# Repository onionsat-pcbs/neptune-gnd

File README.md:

# Neptune GND
Ground Station Module for Project Neptune

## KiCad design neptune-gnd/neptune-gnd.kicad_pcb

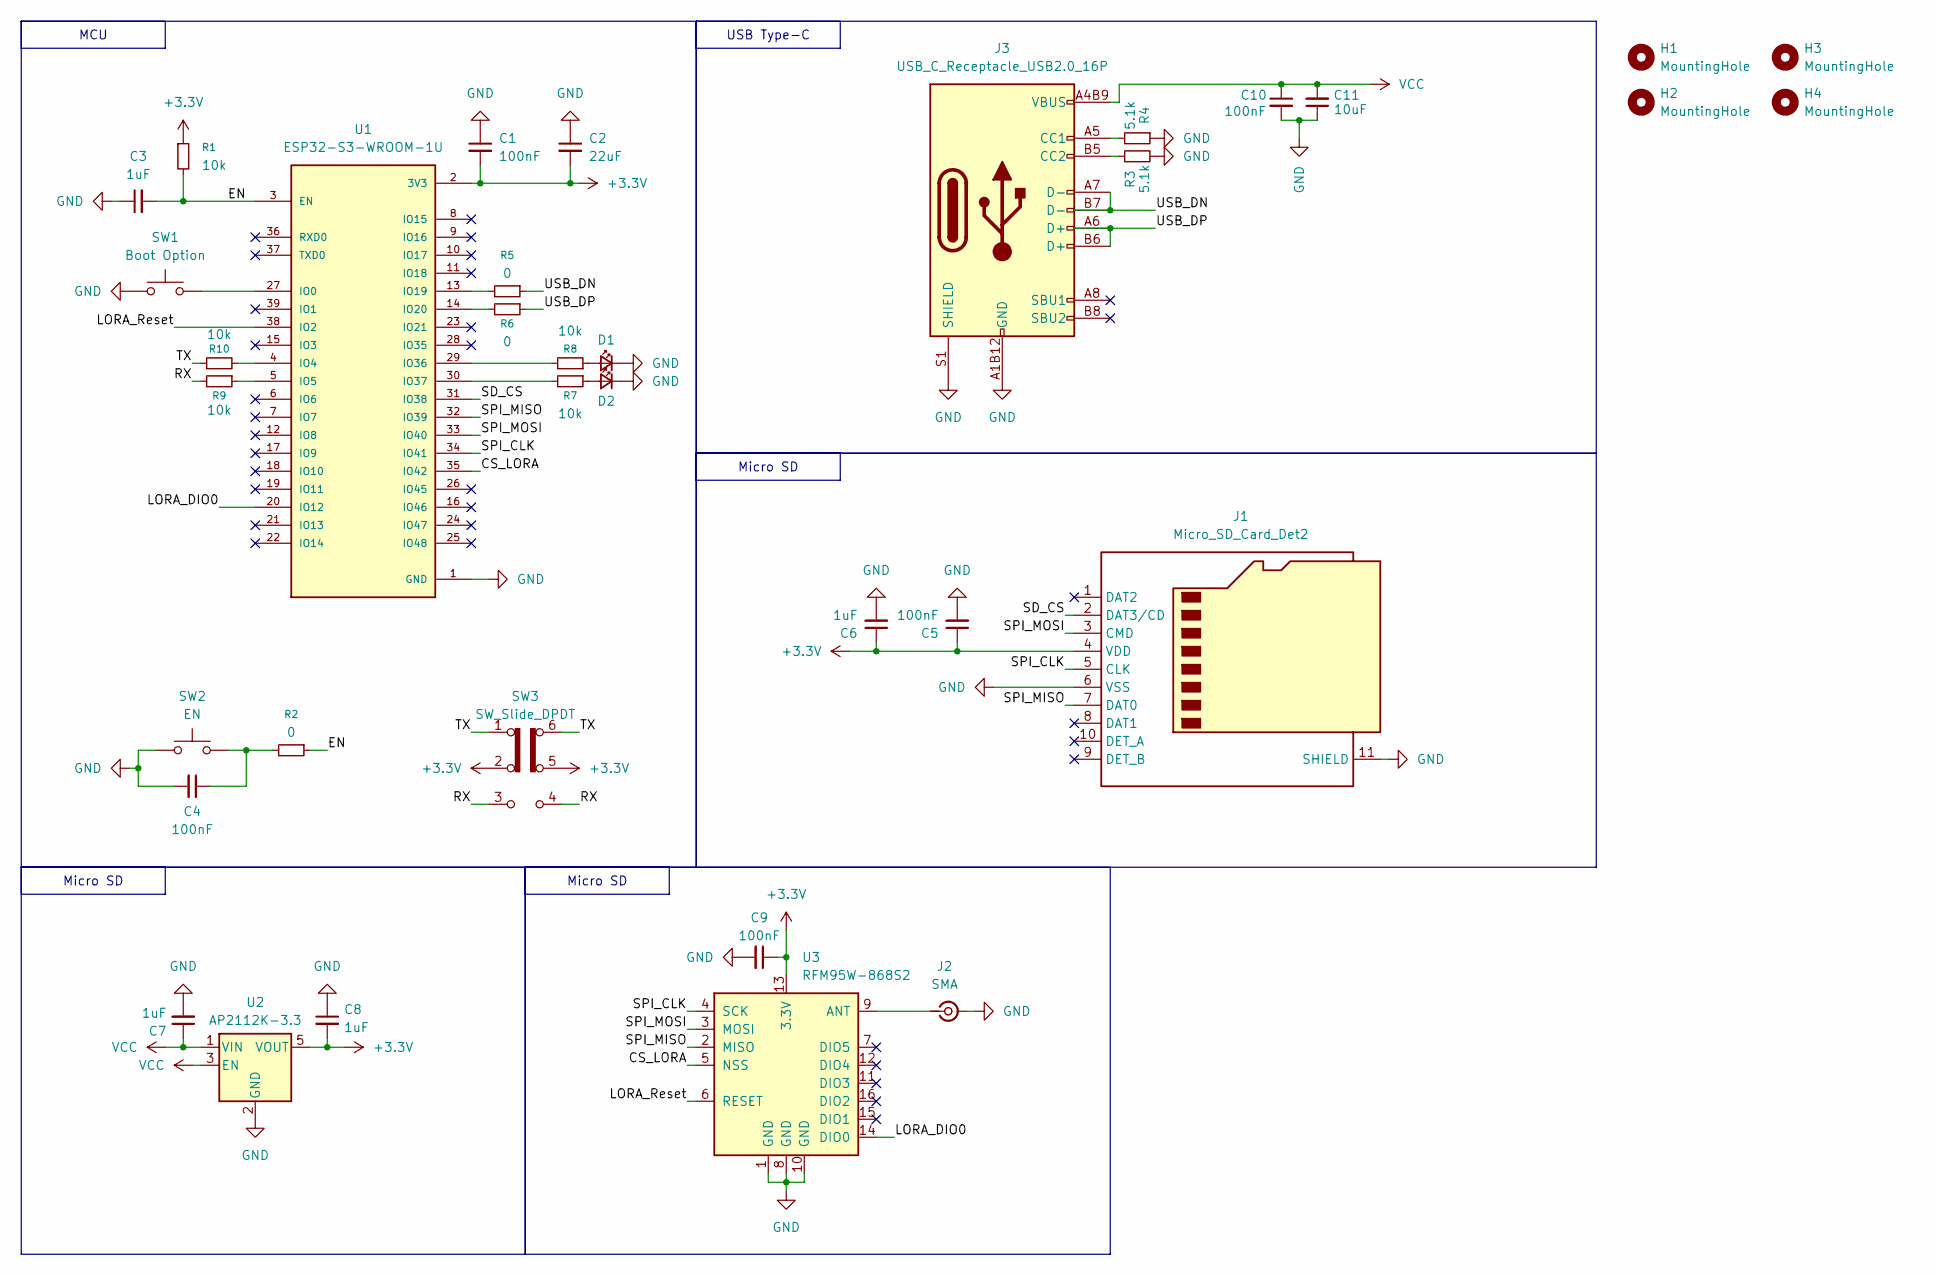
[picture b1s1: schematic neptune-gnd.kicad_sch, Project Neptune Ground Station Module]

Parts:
C1, C4, C5, C9, C10: 100nF; C_0603_1608Metric
C2: 22uF; C_0805_2012Metric
C3, C6, C7, C8: 1uF; C_0603_1608Metric
C11: 10uF; C_0603_1608Metric
D1, D2: LED_Small; LED_0603_1608Metric
H1, H2, H3, H4: MountingHole; MountingHole_2.2mm_M2_DIN965_Pad_TopBottom
J1: Micro_SD_Card_Det2; microSD_HC_Hirose_DM3D-SF
J2: SMA; SMA-TH_DL-SMA-KWE
J3: USB_C_Receptacle_USB2.0_16P; USB-SMD_TYPE-C-16PQT-073
R1, R7, R8, R9, R10: 10k; R_0603_1608Metric
R2: 0; R_0603_1608Metric
R3, R4: 5.1k; R_0402_1005Metric
R5, R6: 0; R_0402_1005Metric
SW1: Boot Option; KEY-SMD_L4.0-W3.0-LS4.9-1
SW2: EN; KEY-SMD_L4.0-W3.0-LS4.9-1
SW3: SW_Slide_DPDT; MS-22D28-G020
U1: ESP32-S3-WROOM-1U; XCVR_ESP32-S3-WROOM-1U; PARTREV v0.6
U2: AP2112K-3.3; ap2112
U3: RFM95W-868S2; HOPERF_RFM9XW_SMD

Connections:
+3.3V: C1.2, C2.2, C5.1, C6.1, C8.2, C9.1, J1.4 (VDD), R1.1, SW3.2 (B), SW3.5 (B), U1.2 (3V3), U2.5 (VOUT), U3.13 (3.3V)
/CS_LORA: U1.35 (IO42), U3.5 (NSS)
/EN: C3.2, R1.2, R2.1, U1.3 (EN)
/LORA_DIO0: U1.20 (IO12), U3.14 (DIO0)
/LORA_Reset: U1.38 (IO2), U3.6 (RESET)
/RX: R9.2, SW3.3 (C), SW3.4 (A)
/SD_CS: J1.2 (DAT3/CD), U1.31 (IO38)
/SPI_CLK: J1.5 (CLK), U1.34 (IO41), U3.4 (SCK)
/SPI_MISO: J1.7 (DAT0), U1.32 (IO39), U3.2 (MISO)
/SPI_MOSI: J1.3 (CMD), U1.33 (IO40), U3.3 (MOSI)
/TX: R10.1, SW3.1 (A), SW3.6 (C)
/USB_DN: J3.A7 (D-), J3.B7 (D-), R5.1
/USB_DP: J3.A6 (D+), J3.B6 (D+), R6.1
GND: C1.1, C2.1, C3.1, C4.2, C5.2, C6.2, C7.2, C8.1, C9.2, C10.2, C11.1, D1.1 (K), D2.1 (K), J1.6 (VSS), J1.11 (SHIELD), J2.2 (Ext), J3.A1B12 (GND), J3.B1A12 (GND), J3.S1 (SHIELD), R3.2, R4.1, SW1.1, SW2.1, U1.1 (GND), U1.40 (GND), U1.41_1 (GND), U1.41_2 (GND), U1.41_3 (GND), U1.41_4 (GND), U1.41_5 (GND), U1.41_6 (GND), U1.41_7 (GND), U1.41_8 (GND), U1.41_9 (GND), U2.2 (GND), U3.1 (GND), U3.8 (GND), U3.10 (GND)
unnamed: C4.1, R2.2, SW2.2
unnamed: D1.2 (A), R8.1
unnamed: D2.2 (A), R7.1
unnamed: J2.1 (In), U3.9 (ANT)
unnamed: J3.A5 (CC1), R4.2
unnamed: J3.B5 (CC2), R3.1
unnamed: SW1.2, U1.27 (IO0)
unnamed: R10.2, U1.4 (IO4)
unnamed: R9.1, U1.5 (IO5)
unnamed: R5.2, U1.13 (IO19)
unnamed: R6.2, U1.14 (IO20)
unnamed: R8.2, U1.29 (IO36)
unnamed: R7.2, U1.30 (IO37)
VCC: C7.1, C10.1, C11.2, J3.A4B9 (VBUS), J3.B4A9 (VBUS), U2.1 (VIN), U2.3 (EN)

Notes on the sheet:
Micro SD
USB Type-C
MCU

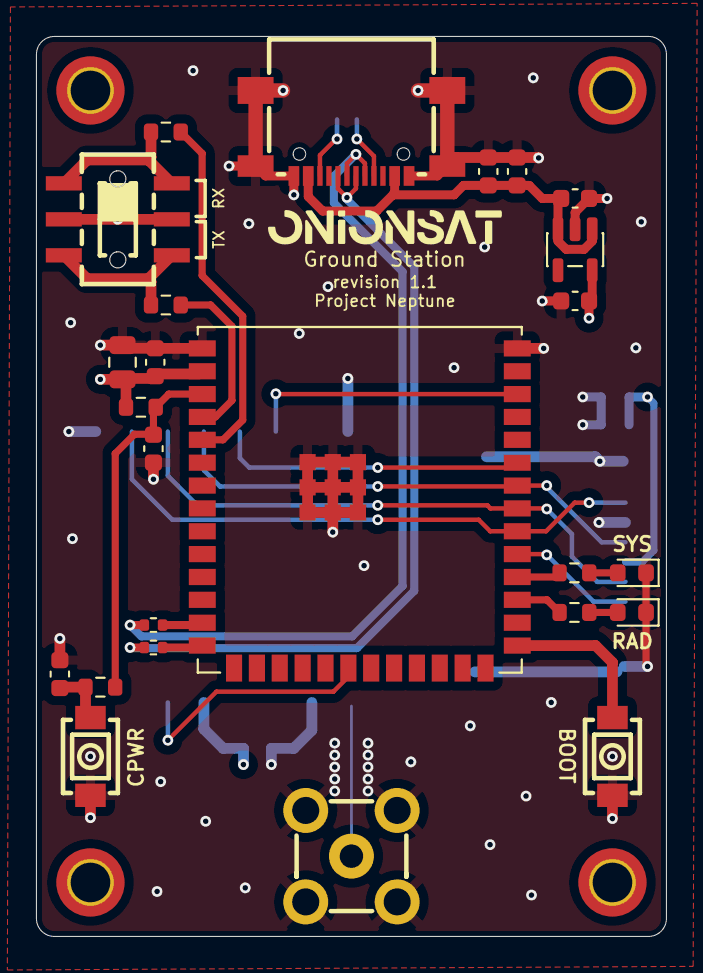
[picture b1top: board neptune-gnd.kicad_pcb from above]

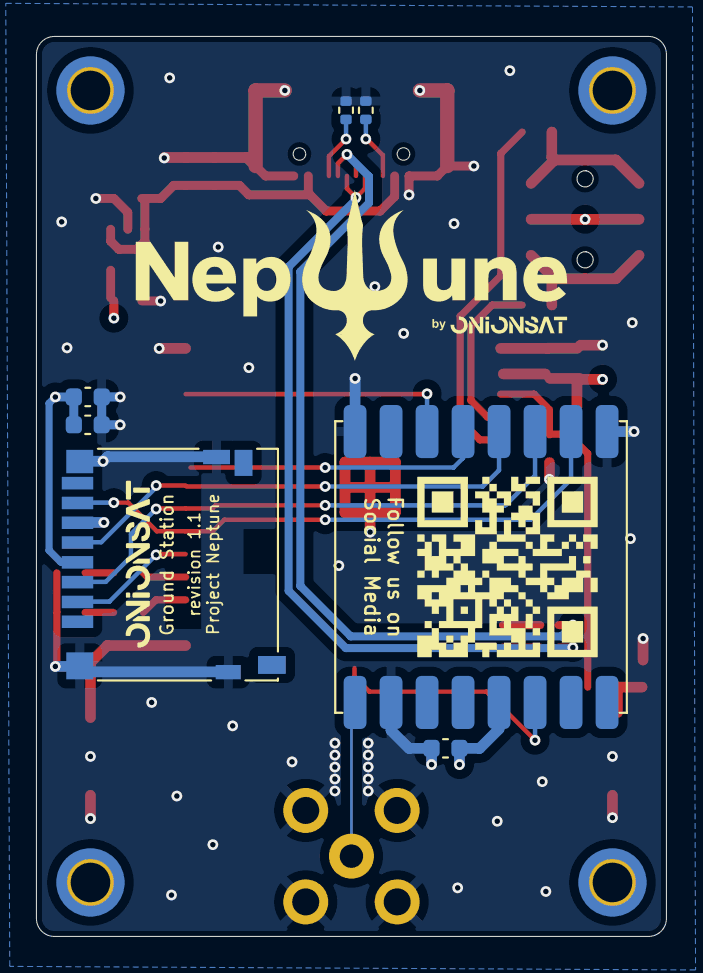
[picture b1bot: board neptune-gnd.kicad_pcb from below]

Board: 4 copper layers, 35.0 x 50.0 mm, 36 parts (7 on the bottom side), 28 nets.

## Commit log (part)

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2025-12-14 Update project name formatting in README
2025-12-14 almost ready
2025-12-15 fixing DRC problems, rerouting start
2025-12-15 send to production
2025-12-28 v1.1 - adding interrupt conn
2025-12-28 silkscreen fix ver number
